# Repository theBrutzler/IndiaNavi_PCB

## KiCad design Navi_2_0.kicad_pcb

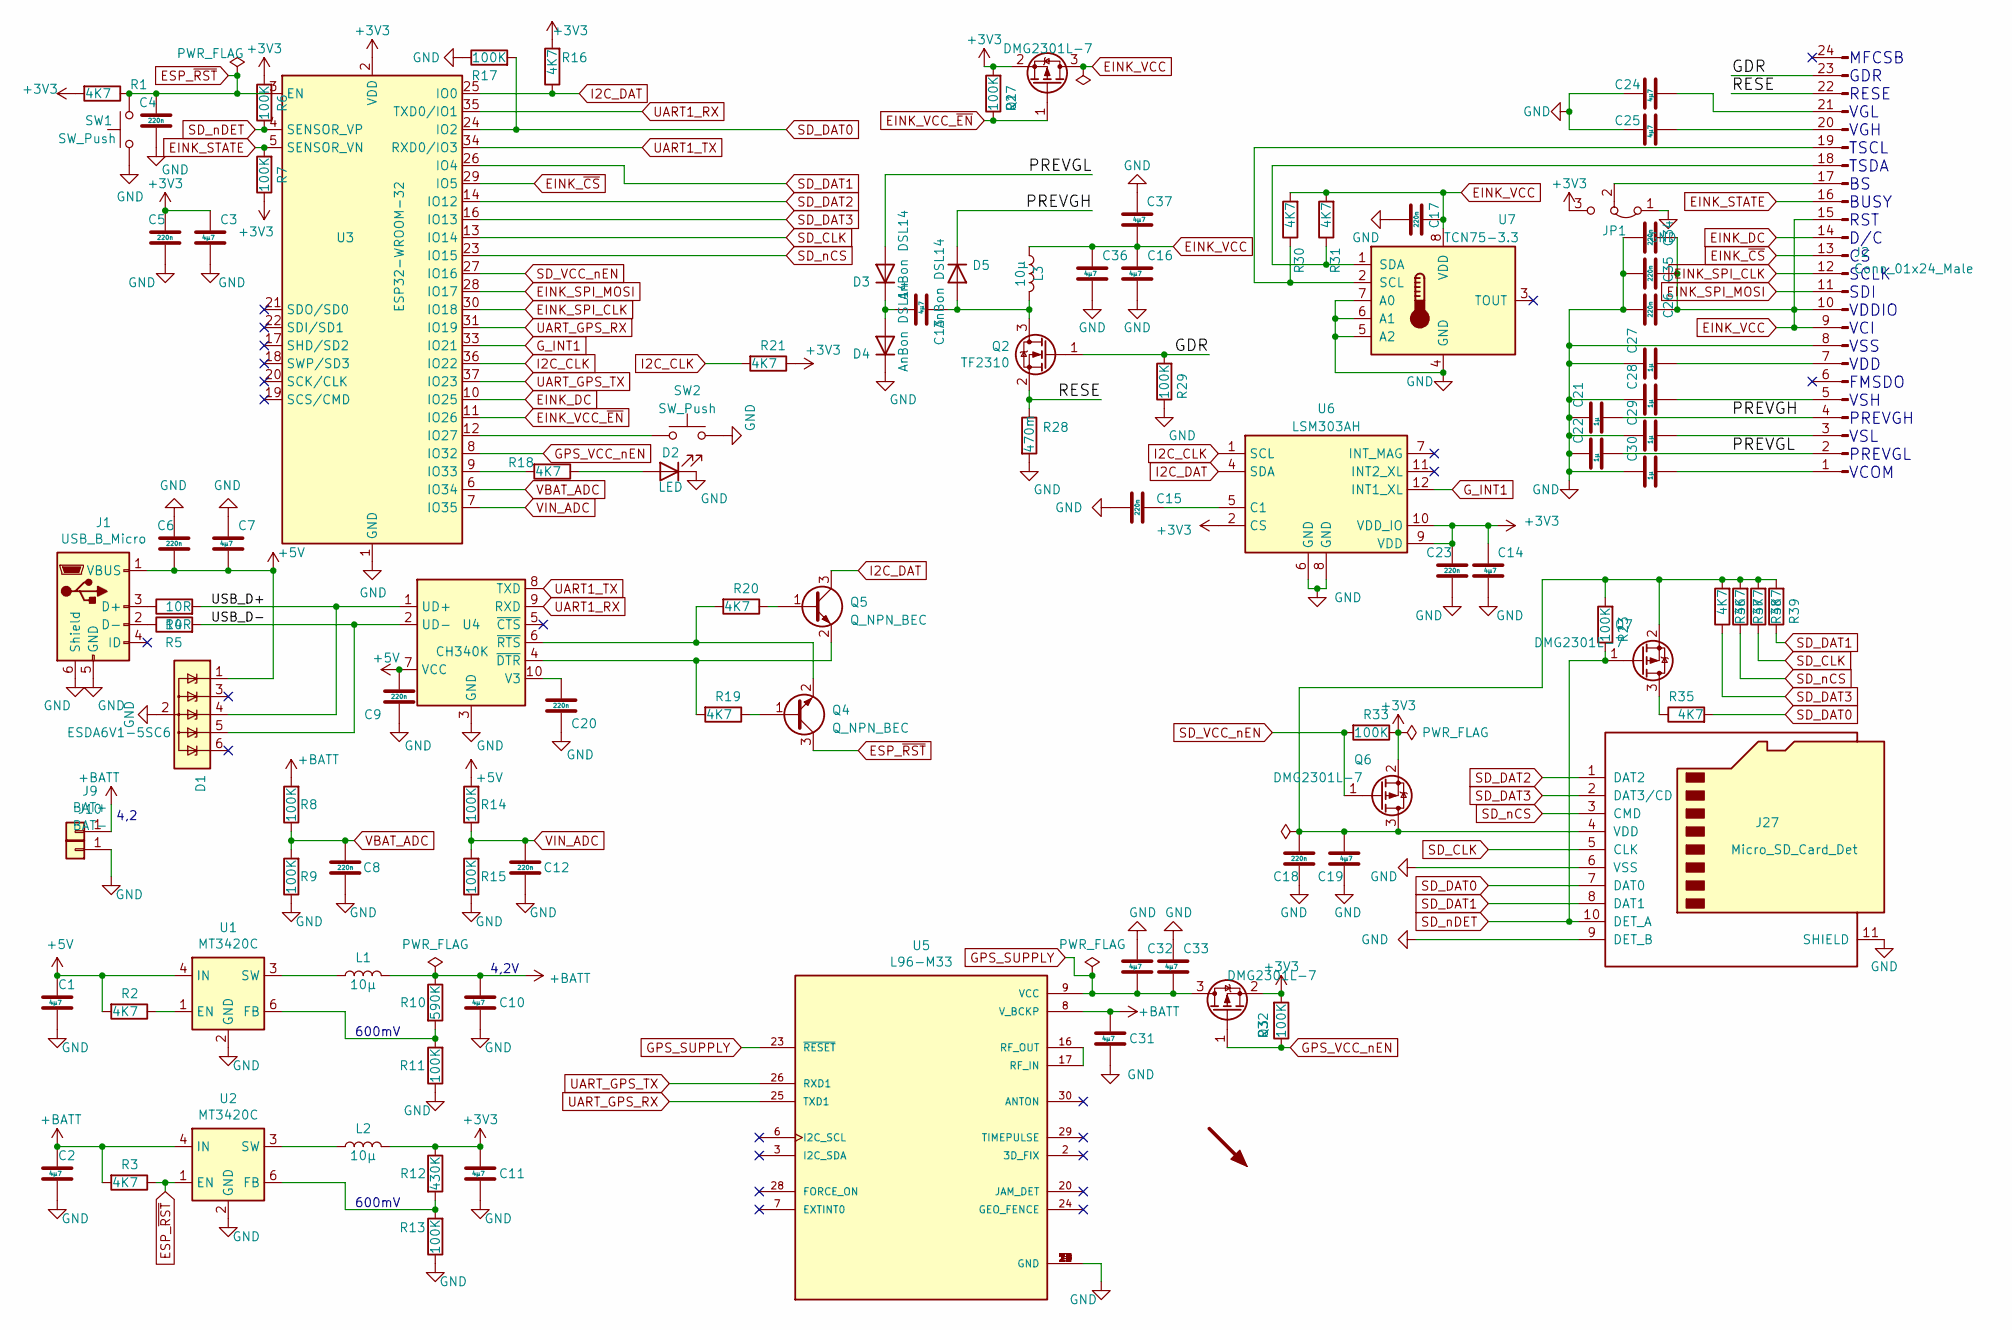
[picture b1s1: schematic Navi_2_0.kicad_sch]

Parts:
C1, C2, C3, C7, C10, C11, C14, C16, C19, C31, C32, C33, C36, C37: 4µ7; C_0603_1608Metric; LCSC C415373
C4, C5, C6, C8, C9, C12, C15, C17, C18, C20, C23, C26, C34, C35: 220n; C_0603_1608Metric; LCSC C163696
C13, C24, C25: 4µ7; C_1206_3216Metric; LCSC C77096
C21, C22, C27, C28, C29, C30: 1µ; C_0603_1608Metric; LCSC C92796
D1: ESDA6V1-5SC6; SOT-23-6; LCSC C2827672
D2: LED; LED_0603_1608Metric_Castellated; LCSC C965799
D3, D4, D5: AnBon DSL14; D_SOD-123F; LCSC C397616
DISPLAY1: SYM_Arrow45_Large; EPD_MODUL 5.65
J1: USB_B_Micro; MICRO QTZB5.0; LCSC C2681556
J2: Conn_01x24_Male; Hirose_FH12-24S-0.5SH_1x24-1MP_P0.50mm_Horizontal; LCSC C283126
J9: BAT+; TestPoint_Pad_D3.0mm
J10: BAT-; TestPoint_Pad_3.0x3.0mm
J27: Micro_SD_Card_Det; microSD_HC_Molex_104031-0811; LCSC ??
JP1: Jumper_3_Bridged12; SolderJumper-3_P1.3mm_Bridged2Bar12_Pad1.0x1.5mm
L1, L2, L3: 10µ; L_Bourns-SRN4018; LCSC C520273
Q1, Q3, Q6, Q7: DMG2301L-7; TSOT-23; LCSC C508195
Q2: TF2310; SOT-23; LCSC C436854
Q4, Q5: Q_NPN_BEC; SOT-23; LCSC C181167
R1, R2, R3, R16, R18, R19, R20, R21, R30, R31, R35, R36, R37, R38, R39: 4K7; R_0603_1608Metric; LCSC C105428
R4, R5: 10R; R_0603_1608Metric; LCSC C217691
R6, R7, R8, R9, R11, R13, R14, R15, R17, R23, R27, R29, R32, R33: 100K; R_0603_1608Metric; LCSC C15458
R10: 590K; R_0603_1608Metric; LCSC C23208
R12: 430K; R_0603_1608Metric; LCSC C170597
R28: 470m; R_0805_2012Metric; LCSC C25040
SW1, SW2: SW_Push; SW_DIP_SPSTx01_Slide_Copal_CHS-01B_W7.62mm_P1.27mm; LCSC !!
U1, U2: MT3420C; SOT-23-6; LCSC C181741
U3: ESP32-WROOM-32; LCSC C82899
U4: CH340K; SSOP-10_EP1_3.9x4.9mm_P1.00mm; LCSC C968586
U5: L96-M33; XCVR_L96-M33; LCSC !!
U6: LSM303AH; LGA-12_2x2mm_P0.5mm; LCSC !!
U7: TCN75-3.3; SOIC-8_3.9x4.9mm_P1.27mm; LCSC !!

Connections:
+3V3: C3.1, C5.1, C11.1, C14.2, C23.1, JP1.3 (B), L2.2, Q1.2 (S), Q3.2 (S), Q6.2 (S), R1.2, R6.2, R7.1, R12.1, R16.2, R21.1, R27.2, R32.2, R33.1, U3.2 (VDD), U6.2 (CS), U6.9 (VDD), U6.10 (VDD_IO)
+5V: C1.1, C6.2, C7.2, C9.1, D1.1 (IO1), J1.1 (VBUS), R2.2, R14.2, U1.4 (IN), U4.7 (VCC)
+BATT: C2.1, C10.1, C31.1, J9.1, L1.2, R3.2, R8.2, R10.1, U2.4 (IN), U5.8 (V_BCKP)
/GDR: J2.23, Q2.1 (G), R29.2
/PREVGH: C21.2, D5.1 (K), J2.4
/PREVGL: C22.2, D3.2 (A), J2.2
/RESE: J2.22, Q2.2 (S), R28.1
/USB_D+: D1.4 (IO3), R4.2, U4.1 (UD+)
/USB_D-: D1.5 (IO4), R5.2, U4.2 (UD-)
EINK_DC: J2.14, U3.10 (IO25)
EINK_SPI_CLK: J2.12, U3.30 (IO18)
EINK_SPI_MOSI: J2.11, U3.28 (IO17)
EINK_STATE: J2.16, R7.2, U3.5 (SENSOR_VN)
EINK_VCC: C16.1, C17.1, C26.1, C34.1, C35.1, C36.1, C37.1, J2.9, J2.10, J2.15, L3.1, Q1.3 (D), R30.2, R31.2, U7.8 (VDD)
EINK_VCC_~EN: Q1.1 (G), R27.1, U3.11 (IO26)
EINK_~CS: J2.13, U3.29 (IO5)
ESP_~RST: C4.1, Q4.3 (C), R1.1, R3.1, SW1.2, U2.1 (EN), U3.3 (EN)
GND: C1.2, C2.2, C3.2, C4.2, C5.2, C6.1, C7.1, C8.1, C9.2, C10.2, C11.2, C12.1, C14.1, C15.2, C16.2, C17.2, C18.2, C19.1, C20.2, C21.1, C22.1, C23.2, C24.1, C25.1, C26.2, C27.1, C28.1, C29.1, C30.1, C31.2, C32.1, C33.1, C34.2, C35.2, C36.2, C37.2, D1.2 (GND), D2.1 (K), D4.1 (K), J1.5 (GND), J1.6 (Shield), J2.8, J10.1, J27.6 (VSS), J27.9 (DET_B), J27.11 (SHIELD), JP1.1 (A), R9.1, R11.1, R13.1, R15.1, R17.1, R28.2, R29.1, SW1.1, SW2.2, U1.2 (GND), U2.2 (GND), U3.1 (GND), U3.15 (GND), U3.38 (GND), U3.39 (GND), U4.3 (GND), U4.PAD (GND), U5.4 (GND), U5.5 (GND), U5.10 (GND), U5.11 (GND), U5.12 (GND), U5.13 (GND), U5.14 (GND), U5.15 (GND), U5.18 (GND), U5.19 (GND), U5.21 (GND), U5.22 (GND), U5.27 (GND), U5.31 (GND), U6.6 (GND), U6.8 (GND), U7.4 (GND), U7.5 (A2), U7.6 (A1), U7.7 (A0)
GPS_SUPPLY: C32.2, C33.2, Q3.3 (D), U5.9 (VCC), U5.23 (~RESET)
GPS_VCC_nEN: Q3.1 (G), R32.1, U3.8 (IO32)
G_INT1: U3.33 (IO21), U6.12 (INT1_XL)
I2C_CLK: R21.2, U3.36 (IO22), U6.1 (SCL)
I2C_DAT: Q5.3 (C), R16.1, U3.25 (IO0), U6.4 (SDA)
unnamed: C13.1, D5.2 (A), L3.2, Q2.3 (D)
unnamed: C13.2, D3.1 (K), D4.2 (A)
unnamed: C15.1, U6.5 (C1)
unnamed: C18.1, C19.2, J27.4 (VDD), Q6.3 (D), Q7.2 (S), R23.2, R36.2, R37.2, R38.2, R39.2
unnamed: C20.1, U4.10 (V3)
unnamed: C24.2, J2.21
unnamed: C25.2, J2.20
unnamed: C27.2, J2.7
unnamed: C28.2, J2.5
unnamed: C29.2, J2.3
unnamed: C30.2, J2.1
unnamed: D2.2 (A), R18.1
unnamed: J1.2 (D-), R5.1
unnamed: J1.3 (D+), R4.1
unnamed: J2.17, JP1.2 (C)
unnamed: J2.18, R31.1, U7.1 (SDA)
unnamed: J2.19, R30.1, U7.2 (SCL)
unnamed: L1.1, U1.3 (SW)
unnamed: L2.1, U2.3 (SW)
unnamed: Q4.1 (B), R19.1
unnamed: Q4.2 (E), R20.2, U4.6 (~RTS)
unnamed: Q5.1 (B), R20.1
unnamed: Q5.2 (E), R19.2, U4.4 (~DTR)
unnamed: Q7.3 (D), R35.1
unnamed: R2.1, U1.1 (EN)
unnamed: R10.2, R11.2, U1.6 (FB)
unnamed: R12.2, R13.2, U2.6 (FB)
unnamed: R18.2, U3.9 (IO33)
unnamed: SW2.1, U3.12 (IO27)
unnamed: U5.16 (RF_OUT), U5.17 (RF_IN)
SD_CLK: J27.5 (CLK), R38.1, U3.13 (IO14)
SD_DAT0: J27.7 (DAT0), R17.2, R35.2, U3.24 (IO2)
SD_DAT1: J27.8 (DAT1), R39.1, U3.26 (IO4)
SD_DAT2: J27.1 (DAT2), U3.14 (IO12)
SD_DAT3: J27.2 (DAT3/CD), R36.1, U3.16 (IO13)
SD_VCC_nEN: Q6.1 (G), R33.2, U3.27 (IO16)
SD_nCS: J27.3 (CMD), R37.1, U3.23 (IO15)
SD_nDET: J27.10 (DET_A), Q7.1 (G), R6.1, R23.1, U3.4 (SENSOR_VP)
UART1_RX: U3.35 (TXD0/IO1), U4.9 (RXD)
UART1_TX: U3.34 (RXD0/IO3), U4.8 (TXD)
UART_GPS_RX: U3.31 (IO19), U5.25 (TXD1)
UART_GPS_TX: U3.37 (IO23), U5.26 (RXD1)
VBAT_ADC: C8.2, R8.1, R9.2, U3.6 (IO34)
VIN_ADC: C12.2, R14.1, R15.2, U3.7 (IO35)

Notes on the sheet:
4,2
600mV
4,2V
MFCSB GDR RESE VGL VGH TSCL TSDA BS BUSY RST D/C CS SCLK SDI VDDIO VCI VSS VDD FMSDO VSH PREVGH VSL PREVGL VCOM

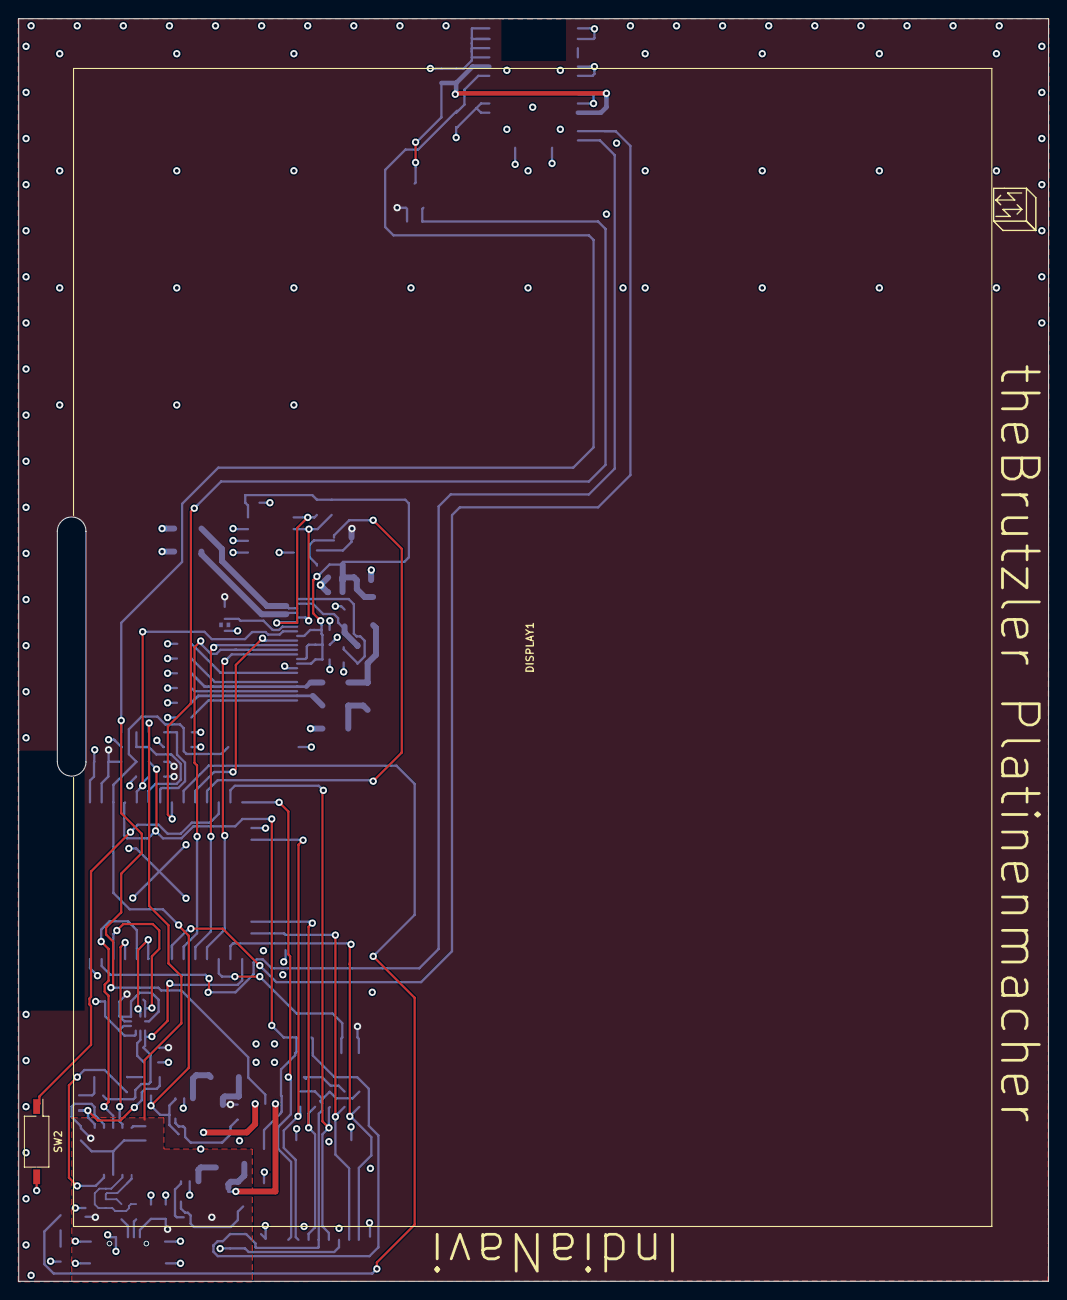
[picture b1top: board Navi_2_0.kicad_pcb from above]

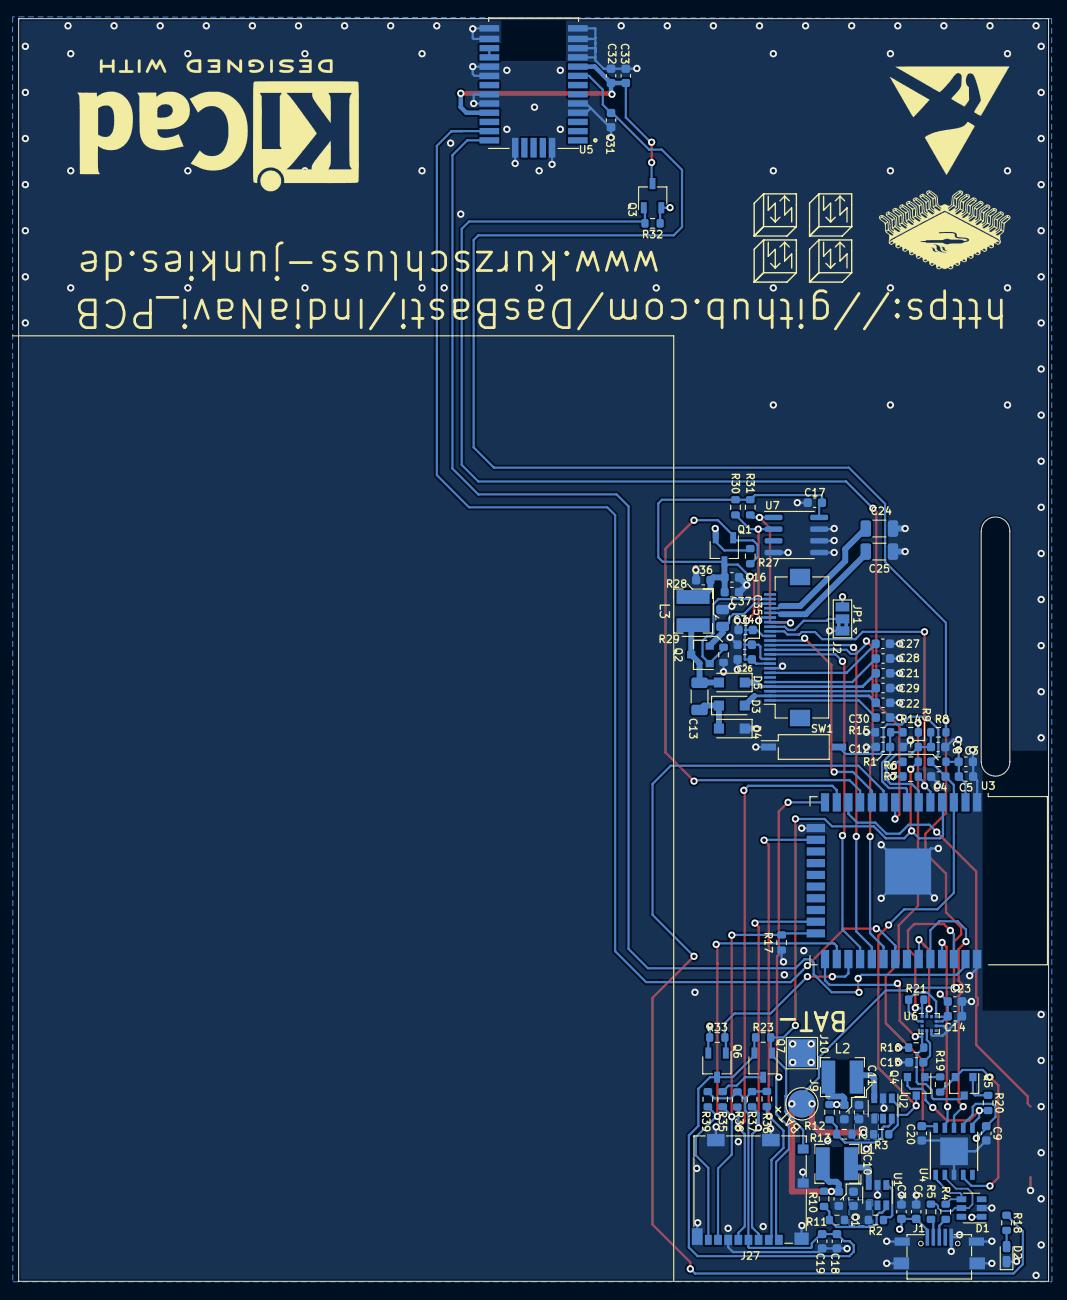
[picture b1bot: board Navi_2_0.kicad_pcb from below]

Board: 4 copper layers, 111.7 x 136.9 mm, 107 parts (104 on the bottom side), 67 nets.

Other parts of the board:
SM3, SM3#2, SM3#3, SM3#4, SM3#5: SYM_Arrow45_Tiny; Symbol_kurzschlussblog

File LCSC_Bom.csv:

Quantity,Manufacture Part Number,Manufacturer(optional),Description(optional),LCSC Part Number(optional),Package(optional),Customer Part Number(optional)
14,4u7,,,C415373,,
14,220n,,,C163696,,
3,4u7,,,C77096,,
6,1u,,,C92796,,
1,ESDA6V1-5SC6,,,C2827672,,
1,LED,,,C965799,,
3,AnBon DSL14,,, 	C397616,,
1,USB_B_Micro,,,C2681556,,
1,Conn_01x24_Male,,,C283126,,
3,10u,,,C520273,,
4,DMG2301L-7 ,,,C508195,,
1,TF2310,,,C436854,,
2,Q_NPN_BEC,,,C181167,,
15,4K7,,,C105428,,
2,10R,,,C217691,,
14,100K,,,C15458,,
1,590K,,,C23208,,
1,430K,,,C170597,,
1,470m,,,C25040,,
2,MT3420C,,,C181741,,
1,ESP32-WROOM-32,,,C82899,,
1,CH340K,,,C968586,,

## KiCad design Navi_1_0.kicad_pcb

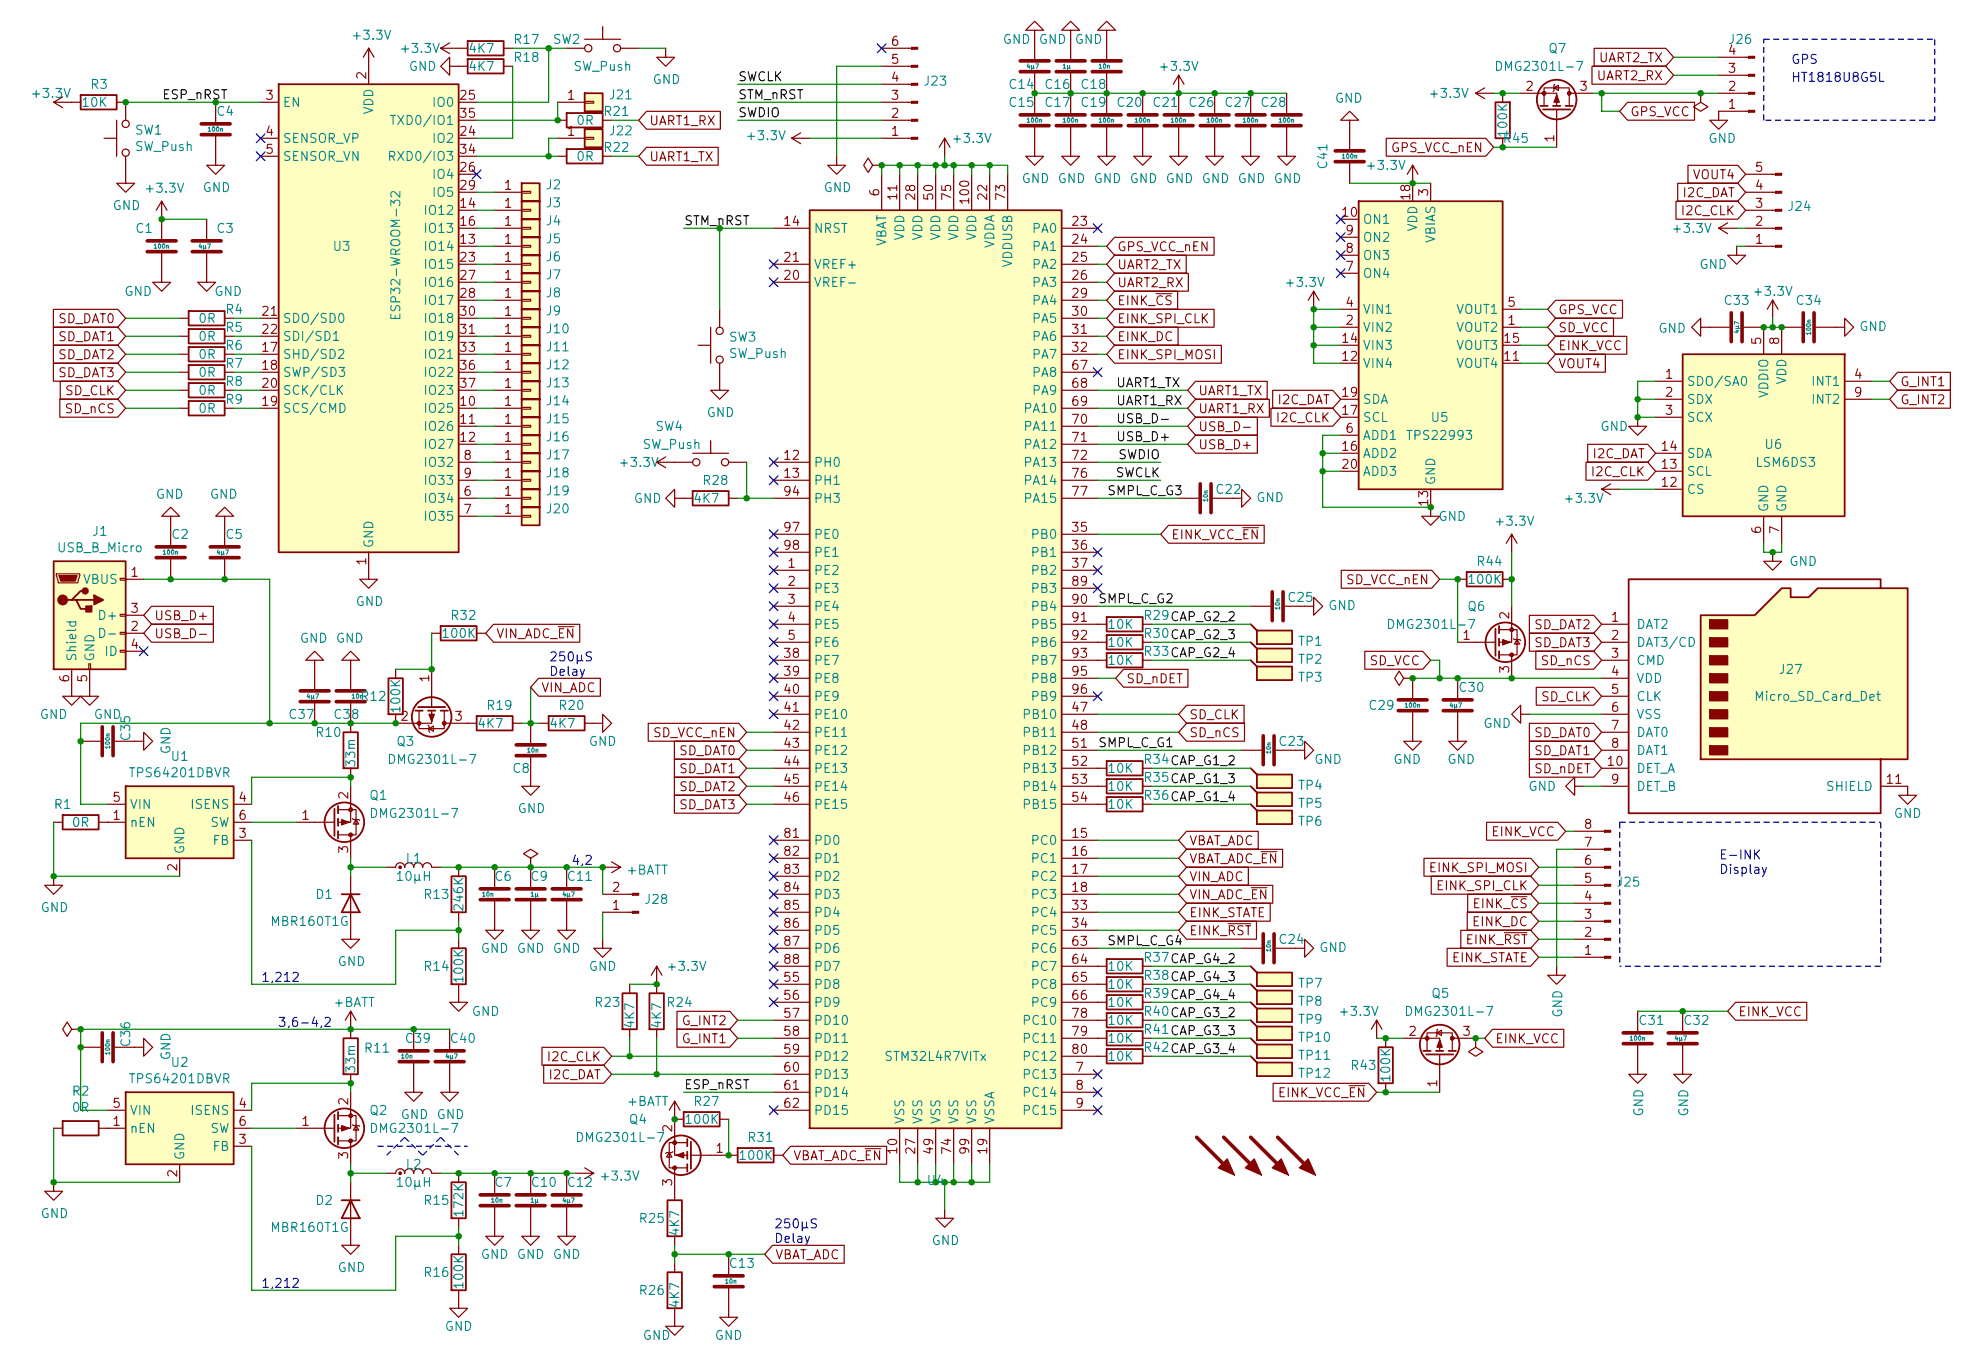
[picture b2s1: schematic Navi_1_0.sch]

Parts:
C1, C2, C4, C15, C17, C19, C20, C21, C26, C27, C28, C29, C31, C34, C35, C36, C41: 100n; C_0603_1608Metric
C3, C5, C11, C12, C14, C30, C32, C33, C37, C40: 4µ7; C_0603_1608Metric
C6, C7, C8, C13, C18, C22, C23, C24, C25, C38, C39: 10n; C_0603_1608Metric
C9, C10, C16: 1µ; C_0603_1608Metric
D1, D2: MBR160T1G; D_SOD-123
J1: USB_B_Micro; USB_Micro-B_Wuerth_629105150521
J2, J3, J4, J5, J6, J7, J8, J9, J10, J11, J12, J13, J14, J15, J16, J17, J18, J19, J20, J21, J22: Conn_01x01; Pin_D0.7mm_L6.5mm_W1.8mm_FlatFork
J23: Conn_01x06_Male; Tag-Connect_TC2030-IDC-FP_2x03_P1.27mm_Vertical
J24: Conn_01x05_Male; PinHeader_1x05_P2.54mm_Vertical
J25: Conn_01x08_Male; PinHeader_1x08_P2.54mm_Vertical
J26: Conn_01x04_Male; PinHeader_1x04_P2.00mm_Vertical
J27: Micro_SD_Card_Det; microSD_HC_Molex_104031-0811
J28: Conn_01x02_Male; PinHeader_1x02_P2.54mm_Vertical
L1, L2: 10µH; L_1210_3225Metric
Q1, Q2, Q3, Q4, Q5, Q6, Q7: DMG2301L-7; TSOT-23
R1, R2, R4, R5, R6, R7, R8, R9, R21, R22: 0R; R_0603_1608Metric
R3, R29, R30, R33, R34, R35, R36, R37, R38, R39, R40, R41, R42: 10K; R_0603_1608Metric
R10, R11: 33m; R_1206_3216Metric
R12, R14, R16, R27, R31, R32, R43, R44, R45: 100K; R_0402_1005Metric
R13: 246K; R_0603_1608Metric
R15: 172K; R_0603_1608Metric
R17, R18, R19, R20, R23, R24, R25, R26, R28: 4K7; R_0603_1608Metric
SW1, SW2, SW3, SW4: SW_Push; SW_Push_1P1T-MP_NO_Horizontal_Alps_SKRTLAE010
TP1, TP2, TP3, TP4, TP5, TP6, TP7, TP8, TP9, TP10, TP11, TP12: TestPoint_Flag
U1, U2: TPS64201DBVR; TSOT-23-6
U3: ESP32-WROOM-32
U4: STM32L4R7VITx; LQFP-100_14x14mm_P0.5mm
U5: TPS22993; Texas_S-PWQFN-N20
U6: LSM6DS3; LGA-14_3x2.5mm_P0.5mm_LayoutBorder3x4y

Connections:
+3V3: C1.1, C3.1, C7.1, C10.1, C12.1, C14.1, C15.1, C16.1, C17.1, C18.1, C19.1, C20.1, C21.1, C26.1, C27.1, C28.1, C33.2, C34.2, C41.2, J23.1, J24.2, L2.2, Q5.2 (S), Q6.2 (S), Q7.2 (S), R3.2, R15.1, R17.2, R23.1, R24.1, R43.1, R44.1, R45.2, SW4.1, U3.2 (VDD), U4.6 (VBAT), U4.11 (VDD), U4.22 (VDDA), U4.28 (VDD), U4.50 (VDD), U4.73 (VDDUSB), U4.75 (VDD), U4.100 (VDD), U5.2 (VIN2), U5.3 (VBIAS), U5.4 (VIN1), U5.12 (VIN4), U5.14 (VIN3), U5.18 (VDD), U6.5 (VDDIO), U6.8 (VDD), U6.12 (CS)
+BATT: C6.1, C9.1, C11.1, C36.2, C39.1, C40.1, J28.2, L1.2, Q4.2 (S), R11.1, R13.1, R27.2, U2.5 (VIN)
/CAP_G1_2: R34.1, TP4.1
/CAP_G1_3: R35.1, TP5.1
/CAP_G1_4: R36.1, TP6.1
/CAP_G2_2: R29.1, TP1.1
/CAP_G2_3: R30.1, TP2.1
/CAP_G2_4: R33.1, TP3.1
/CAP_G3_2: R40.1, TP10.1
/CAP_G3_3: R41.1, TP11.1
/CAP_G3_4: R42.1, TP12.1
/CAP_G4_2: R37.1, TP7.1
/CAP_G4_3: R38.1, TP8.1
/CAP_G4_4: R39.1, TP9.1
/ESP_nRST: C4.1, R3.1, SW1.2, U3.3 (EN), U4.61 (PD14)
/SMPL_C_G1: C23.1, U4.51 (PB12)
/SMPL_C_G2: C25.1, U4.90 (PB4)
/SMPL_C_G3: C22.1, U4.77 (PA15)
/SMPL_C_G4: C24.1, U4.63 (PC6)
/STM_nRST: J23.3, SW3.2, U4.14 (NRST)
/SWCLK: J23.4, U4.76 (PA14)
/SWDIO: J23.2, U4.72 (PA13)
EINK_DC: J25.3, U4.31 (PA6)
EINK_SPI_CLK: J25.5, U4.30 (PA5)
EINK_SPI_MOSI: J25.6, U4.32 (PA7)
EINK_STATE: J25.1, U4.33 (PC4)
EINK_VCC: C31.1, C32.1, J25.8, Q5.3 (D), U5.15 (VOUT3)
EINK_VCC_~EN: Q5.1 (G), R43.2, U4.35 (PB0)
EINK_~CS: J25.4, U4.29 (PA4)
EINK_~RST: J25.2, U4.34 (PC5)
GND: C1.2, C2.1, C3.2, C4.2, C5.1, C6.2, C7.2, C8.2, C9.2, C10.2, C11.2, C12.2, C13.2, C14.2, C15.2, C16.2, C17.2, C18.2, C19.2, C20.2, C21.2, C22.2, C23.2, C24.2, C25.2, C26.2, C27.2, C28.2, C29.2, C30.2, C31.2, C32.2, C33.1, C34.1, C35.1, C36.1, C37.2, C38.2, C39.2, C40.2, C41.1, D1.2 (A), D2.2 (A), J1.5 (GND), J1.6 (Shield), J23.5, J24.1, J25.7, J26.1, J27.6 (VSS), J27.9 (DET_B), J27.11 (SHIELD), J28.1, R1.2, R2.2, R14.2, R16.2, R18.2, R20.1, R26.2, R28.2, SW1.1, SW2.1, SW3.1, U1.2 (GND), U2.2 (GND), U3.1 (GND), U3.15 (GND), U3.38 (GND), U3.39 (GND), U4.10 (VSS), U4.19 (VSSA), U4.27 (VSS), U4.49 (VSS), U4.74 (VSS), U4.99 (VSS), U5.6 (ADD1), U5.13 (GND), U5.16 (ADD2), U5.20 (ADD3), U6.1 (SDO/SA0), U6.2 (SDX), U6.3 (SCX), U6.6 (GND), U6.7 (GND)
GPS_VCC: J26.2, Q7.3 (D), U5.5 (VOUT1)
GPS_VCC_nEN: Q7.1 (G), R45.1, U4.24 (PA1)
G_INT1: U4.58 (PD11), U6.4 (INT1)
G_INT2: U4.57 (PD10), U6.9 (INT2)
I2C_CLK: J24.3, R23.2, U4.59 (PD12), U5.17 (SCL), U6.13 (SCL)
I2C_DAT: J24.4, R24.2, U4.60 (PD13), U5.19 (SDA), U6.14 (SDA)
unnamed: C2.2, C5.2, C35.2, C37.1, C38.1, J1.1 (VBUS), Q3.2 (S), R10.1, R12.2, U1.5 (VIN)
unnamed: D1.1 (K), L1.1, Q1.3 (D)
unnamed: D2.1 (K), L2.1, Q2.3 (D)
unnamed: J2.1, U3.29 (IO5)
unnamed: J3.1, U3.14 (IO12)
unnamed: J4.1, U3.16 (IO13)
unnamed: J5.1, U3.13 (IO14)
unnamed: J6.1, U3.23 (IO15)
unnamed: J7.1, U3.27 (IO16)
unnamed: J8.1, U3.28 (IO17)
unnamed: J9.1, U3.30 (IO18)
unnamed: J10.1, U3.31 (IO19)
unnamed: J11.1, U3.33 (IO21)
unnamed: J12.1, U3.36 (IO22)
unnamed: J13.1, U3.37 (IO23)
unnamed: J14.1, U3.10 (IO25)
unnamed: J15.1, U3.11 (IO26)
unnamed: J16.1, U3.12 (IO27)
unnamed: J17.1, U3.8 (IO32)
unnamed: J18.1, U3.9 (IO33)
unnamed: J19.1, U3.6 (IO34)
unnamed: J20.1, U3.7 (IO35)
unnamed: J21.1, R21.2, U3.35 (TXD0/IO1)
unnamed: J22.1, R22.2, U3.34 (RXD0/IO3)
unnamed: Q1.1 (G), U1.6 (SW)
unnamed: Q1.2 (S), R10.2, U1.4 (ISENS)
unnamed: Q2.1 (G), U2.6 (SW)
unnamed: Q2.2 (S), R11.2, U2.4 (ISENS)
unnamed: Q3.1 (G), R12.1, R32.2
unnamed: Q3.3 (D), R19.2
unnamed: Q4.1 (G), R27.1, R31.2
unnamed: Q4.3 (D), R25.1
unnamed: R1.1, U1.1 (nEN)
unnamed: R2.1, U2.1 (nEN)
unnamed: R4.1, U3.21 (SDO/SD0)
unnamed: R5.1, U3.22 (SDI/SD1)
unnamed: R6.1, U3.17 (SHD/SD2)
unnamed: R7.1, U3.18 (SWP/SD3)
unnamed: R8.1, U3.20 (SCK/CLK)
unnamed: R9.1, U3.19 (SCS/CMD)
unnamed: R13.2, R14.1, U1.3 (FB)
unnamed: R15.2, R16.1, U2.3 (FB)
unnamed: R17.1, SW2.2, U3.25 (IO0)
unnamed: R18.1, U3.24 (IO2)
unnamed: R28.1, SW4.2, U4.94 (PH3)
unnamed: R29.2, U4.91 (PB5)
unnamed: R30.2, U4.92 (PB6)
unnamed: R33.2, U4.93 (PB7)
unnamed: R34.2, U4.52 (PB13)
unnamed: R35.2, U4.53 (PB14)
unnamed: R36.2, U4.54 (PB15)
unnamed: R37.2, U4.64 (PC7)
unnamed: R38.2, U4.65 (PC8)
unnamed: R39.2, U4.66 (PC9)
unnamed: R40.2, U4.78 (PC10)
unnamed: R41.2, U4.79 (PC11)
unnamed: R42.2, U4.80 (PC12)
SD_CLK: J27.5 (CLK), R8.2, U4.47 (PB10)
SD_DAT0: J27.7 (DAT0), R4.2, U4.43 (PE12)
SD_DAT1: J27.8 (DAT1), R5.2, U4.44 (PE13)
SD_DAT2: J27.1 (DAT2), R6.2, U4.45 (PE14)
SD_DAT3: J27.2 (DAT3/CD), R7.2, U4.46 (PE15)
SD_VCC: C29.1, C30.1, J27.4 (VDD), Q6.3 (D), U5.1 (VOUT2)
SD_VCC_nEN: Q6.1 (G), R44.2, U4.42 (PE11)
SD_nCS: J27.3 (CMD), R9.2, U4.48 (PB11)
SD_nDET: J27.10 (DET_A), U4.95 (PB8)
UART1_RX: R21.1, U4.69 (PA10)
UART1_TX: R22.1, U4.68 (PA9)
UART2_RX: J26.3, U4.26 (PA3)
UART2_TX: J26.4, U4.25 (PA2)
USB_D+: J1.3 (D+), U4.71 (PA12)
USB_D-: J1.2 (D-), U4.70 (PA11)
VBAT_ADC: C13.1, R25.2, R26.1, U4.15 (PC0)
VBAT_ADC_~EN: R31.1, U4.16 (PC1)
VIN_ADC: C8.1, R19.1, R20.2, U4.17 (PC2)
VIN_ADC_~EN: R32.1, U4.18 (PC3)
VOUT4: J24.5, U5.11 (VOUT4)

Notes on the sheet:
1,212
4,2
E-INK Display
250µS Delay
HT1818U8G5L
GPS
3,6-4,2

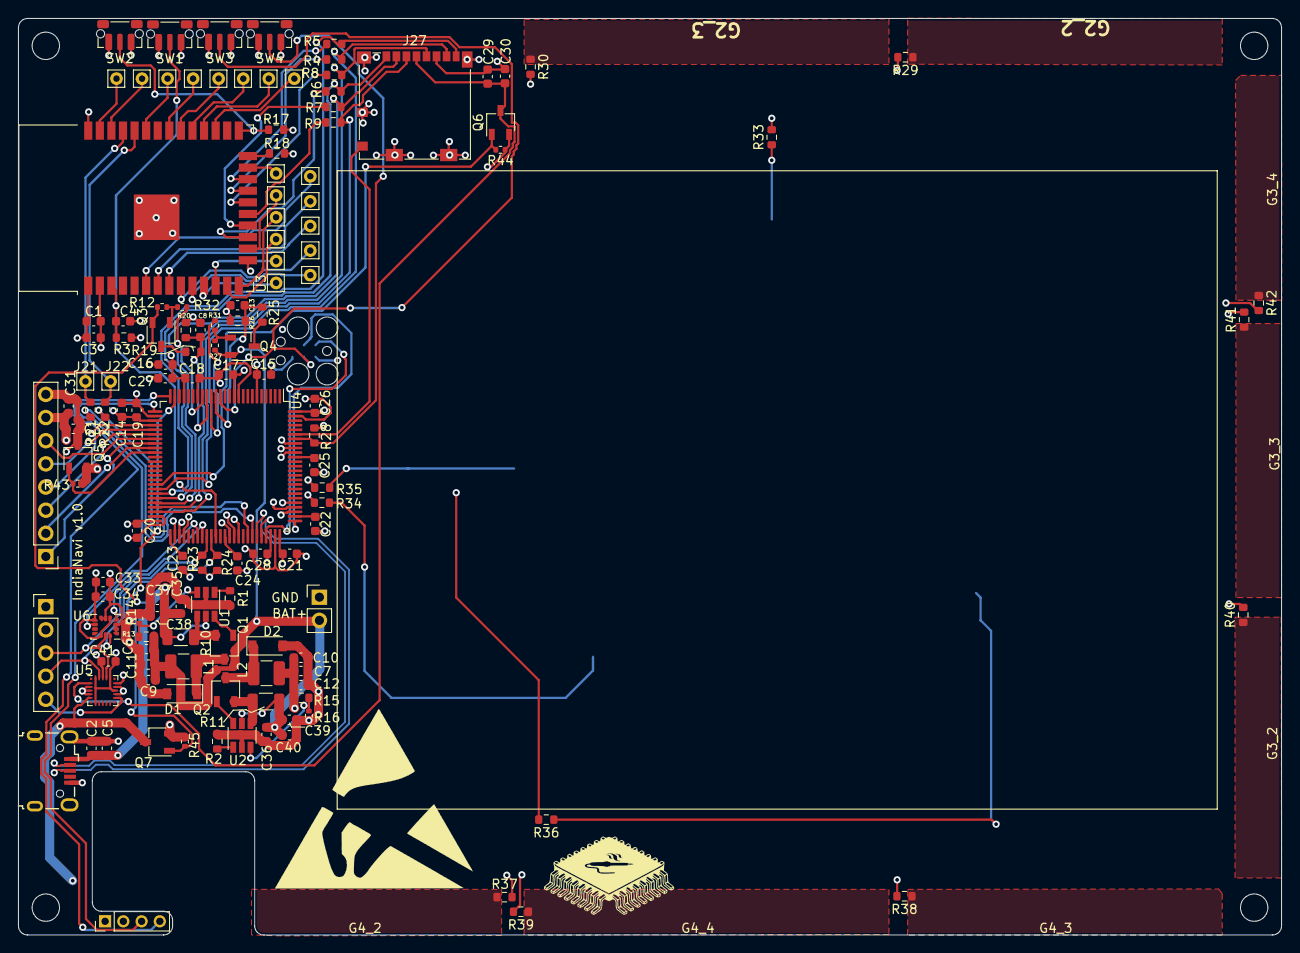
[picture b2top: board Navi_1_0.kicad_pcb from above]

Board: 4 copper layers, 138.5 x 100.5 mm, 135 parts (1 on the bottom side), 102 nets.

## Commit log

2021-05-20 Revision 1 files
2021-05-20 Revision 2 files
2021-05-20 Add gerber files for Rev2 board
2021-05-20 Schematic as PDF
2021-05-23 Update Navi_2_0.kicad_prl
    #1 bearbeitung
2021-05-27 E-Ink Voltages
    #2 Display Spannungen optimiert. Bauteile Verbessert
2021-05-27 #4 Widerstand schaltbar gemacht
    Der Widerstand wurde per MOSFET schaltbar gemacht, da sonst kein Updaten Per UART möglich war
2021-05-27 Again PullUP Widerstand SD Karte
    #4 zum zweitenmal den Pull Up Widerstand ergänzt
2021-05-27 Commit before Layout
    Komm MIT
2021-05-27 Zwischenstand erste Platzierung
    Es fehlen noch die Schaltregler und Reset / Programmierschaltung
2021-06-01 Update G-Sensor
    #9 Ersetzt mit lsm303ah
2021-06-01 Commit vor Routing
    Sicherheitscommit vor routing
2021-06-01 Angefangen zu routen.
    Erstes Routing gestertet. klärung der frage #10
2021-06-04 Layout V3 erster Wurf
    Layout V3 vor DRC
    (Siebdruck und Leiterbahnen fertig)
2021-06-05 changing inductor and connecting reset
    Changed Indoctor 4,7µ to 10µ
    Connected reset button to 3V3 supply enamble regulator #11
2021-06-06 Add Readme an PICs
    Add Readme.md without text
    Add PICs
    Add 3D Models
2021-06-08 Ordered PCB
    Final layout PCB after DRC check ordered.
2021-06-08 Update datasheet Link
    Link to st.com homepage updated
2021-06-10 Image Update
    Image Update 4 content
2021-06-10 3D Model Update
    KiCad could only export wrl 3D models to the complete 3D model (Navi_2_0_step)
    Thats why i reconverted the imported models to wrl and build a new complete model
2021-06-10 Update BOM LCSC
    Generated actual LCSC_BOM.csv to order parts on www.LCSC.com
2021-06-10 Add Case
    Add 3D Model 4 testing
2021-06-30 generate Schematic PDF
2021-10-28 BOM+POS update
    In this Version is a updated bom.csv and pos.csv
